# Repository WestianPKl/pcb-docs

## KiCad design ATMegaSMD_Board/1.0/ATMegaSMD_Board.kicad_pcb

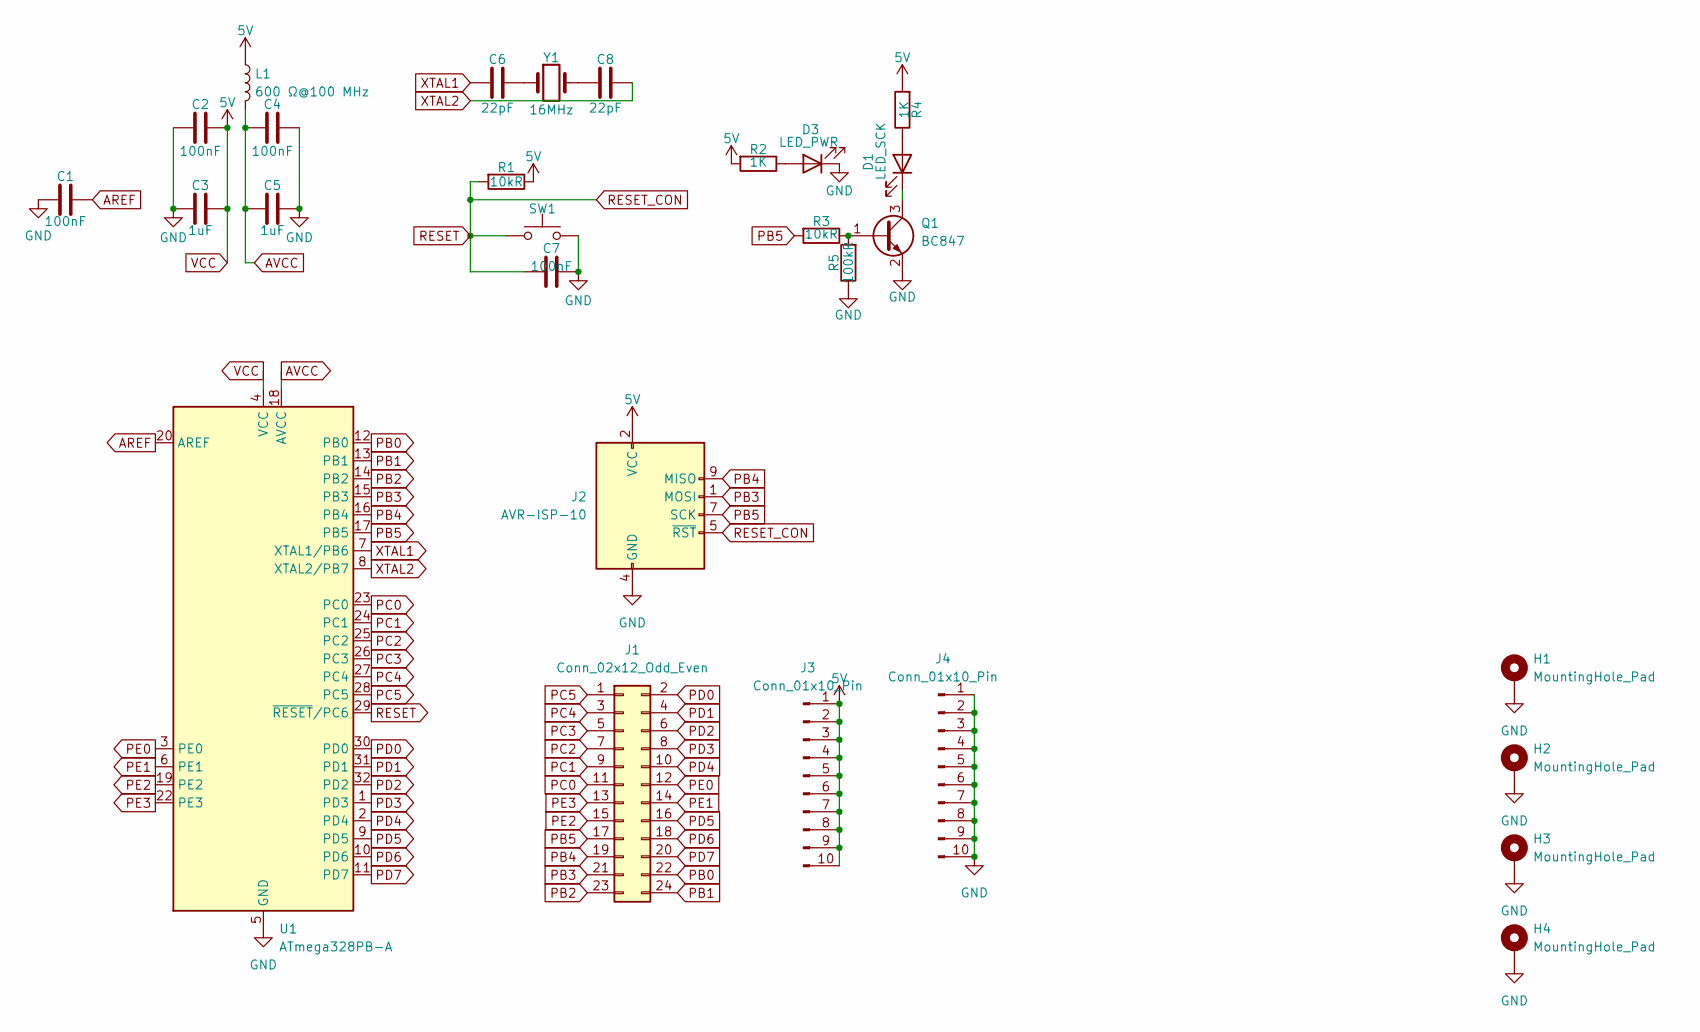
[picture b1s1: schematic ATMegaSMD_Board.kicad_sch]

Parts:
C1, C2, C4, C7: 100nF; C_0805_2012Metric_Pad1.18x1.45mm_HandSolder
C3, C5: 1uF; C_0805_2012Metric_Pad1.18x1.45mm_HandSolder
C6, C8: 22pF; C_0805_2012Metric_Pad1.18x1.45mm_HandSolder
D1: LED_SCK; LED_0805_2012Metric
D3: LED_PWR; LED_0805_2012Metric
H1, H2, H3, H4: MountingHole_Pad; MountingHole_3.2mm_M3_DIN965_Pad
J1: Conn_02x12_Odd_Even; PinHeader_2x12_P2.54mm_Vertical
J2: AVR-ISP-10; IDC-Header_2x05_P2.54mm_Vertical
J3, J4: Conn_01x10_Pin; PinHeader_1x10_P2.54mm_Vertical
L1: 600 Ω@100 MHz; L_0805_2012Metric_Pad1.05x1.20mm_HandSolder
Q1: BC847; SOT-23
R1, R3: 10kR; R_0805_2012Metric
R2, R4: 1K; R_0805_2012Metric
R5: 100kR; R_0805_2012Metric
SW1: Tact Switch 6x6mm / 13mm; SW_PUSH_6mm
U1: ATmega328PB-A; TQFP-32_7x7mm_P0.8mm
Y1: 16MHz; Crystal_HC49-4H_Vertical

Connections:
AREF: C1.2, U1.20 (AREF)
AVCC: C4.1, C5.1, L1.2, U1.18 (AVCC)
GND: C1.1, C2.1, C3.1, C4.2, C5.2, C7.2, D3.1 (K), H1.1, H2.1, H3.1, H4.1, J2.4 (GND), J2.6 (GND), J2.8 (GND), J2.10 (GND), J4.1, J4.2, J4.3, J4.4, J4.5, J4.6, J4.7, J4.8, J4.9, J4.10, Q1.2 (E), R5.1, SW1.2, U1.5 (GND), U1.21 (GND)
unnamed: C6.2, Y1.1
unnamed: C8.1, Y1.2
unnamed: D1.2 (A), R4.1
unnamed: D1.1 (K), Q1.3 (C)
unnamed: D3.2 (A), R2.1
unnamed: Q1.1 (B), R3.1, R5.2
PB0: J1.22, U1.12 (PB0)
PB1: J1.24, U1.13 (PB1)
PB2: J1.23, U1.14 (PB2)
PB3: J1.21, J2.1 (MOSI), U1.15 (PB3)
PB4: J1.19, J2.9 (MISO), U1.16 (PB4)
PB5: J1.17, J2.7 (SCK), R3.2, U1.17 (PB5)
PC0: J1.11, U1.23 (PC0)
PC1: J1.9, U1.24 (PC1)
PC2: J1.7, U1.25 (PC2)
PC3: J1.5, U1.26 (PC3)
PC4: J1.3, U1.27 (PC4)
PC5: J1.1, U1.28 (PC5)
PD0: J1.2, U1.30 (PD0)
PD1: J1.4, U1.31 (PD1)
PD2: J1.6, U1.32 (PD2)
PD3: J1.8, U1.1 (PD3)
PD4: J1.10, U1.2 (PD4)
PD5: J1.16, U1.9 (PD5)
PD6: J1.18, U1.10 (PD6)
PD7: J1.20, U1.11 (PD7)
PE0: J1.12, U1.3 (PE0)
PE1: J1.14, U1.6 (PE1)
PE2: J1.15, U1.19 (PE2)
PE3: J1.13, U1.22 (PE3)
RESET: C7.1, J2.5 (~RST), R1.2, SW1.1, U1.29 (~RESET/PC6)
VCC: C2.2, C3.2, J2.2 (VCC), J3.1, J3.2, J3.3, J3.4, J3.5, J3.6, J3.7, J3.8, J3.9, J3.10, L1.1, R1.1, R2.2, R4.2, U1.4 (VCC)
XTAL1: C6.1, U1.7 (XTAL1/PB6)
XTAL2: C8.2, U1.8 (XTAL2/PB7)

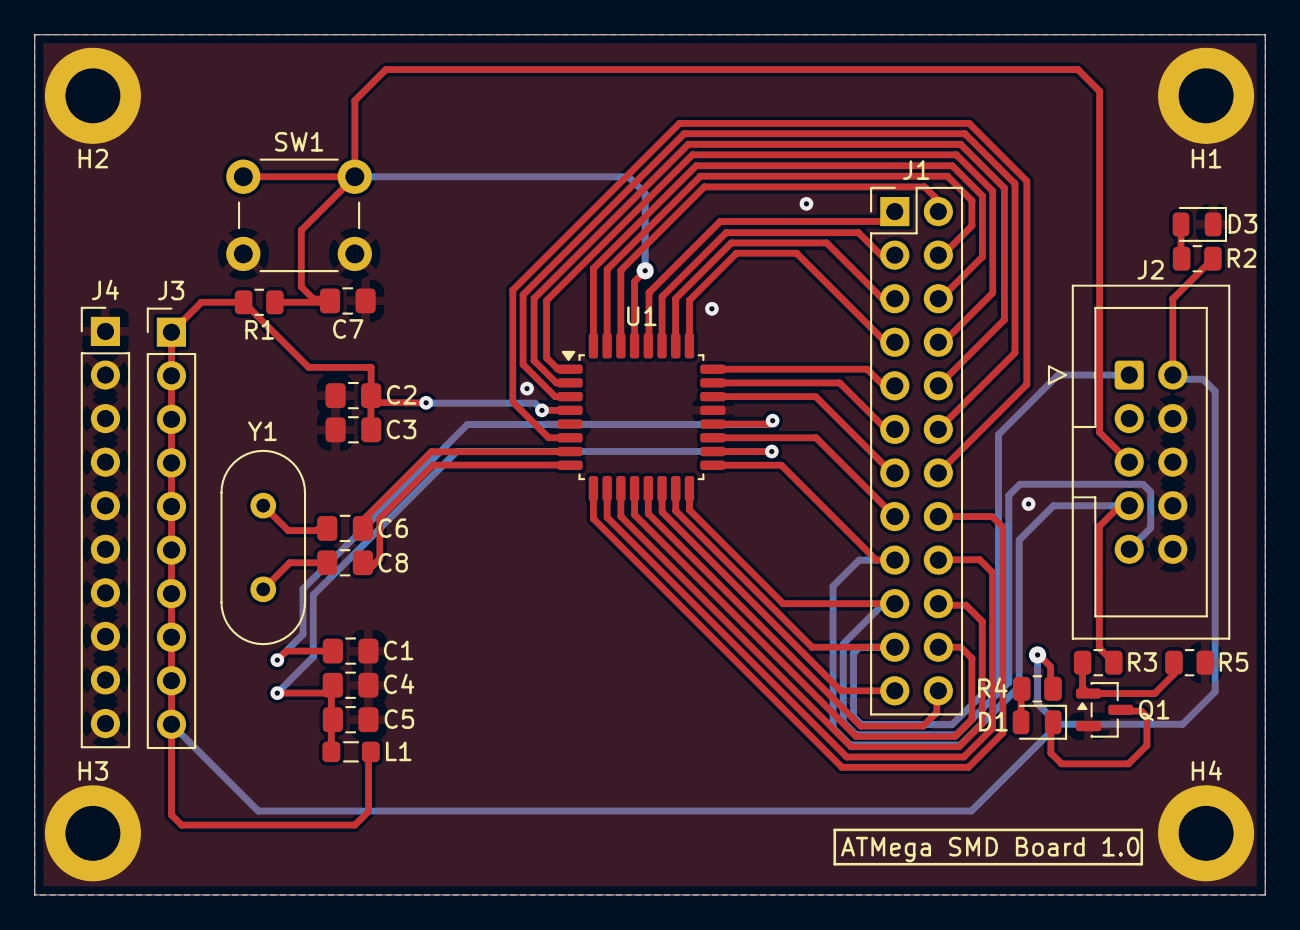
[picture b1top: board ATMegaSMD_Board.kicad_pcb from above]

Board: 2 copper layers, 71.7 x 50.2 mm, 28 parts (0 on the bottom side), 37 nets.

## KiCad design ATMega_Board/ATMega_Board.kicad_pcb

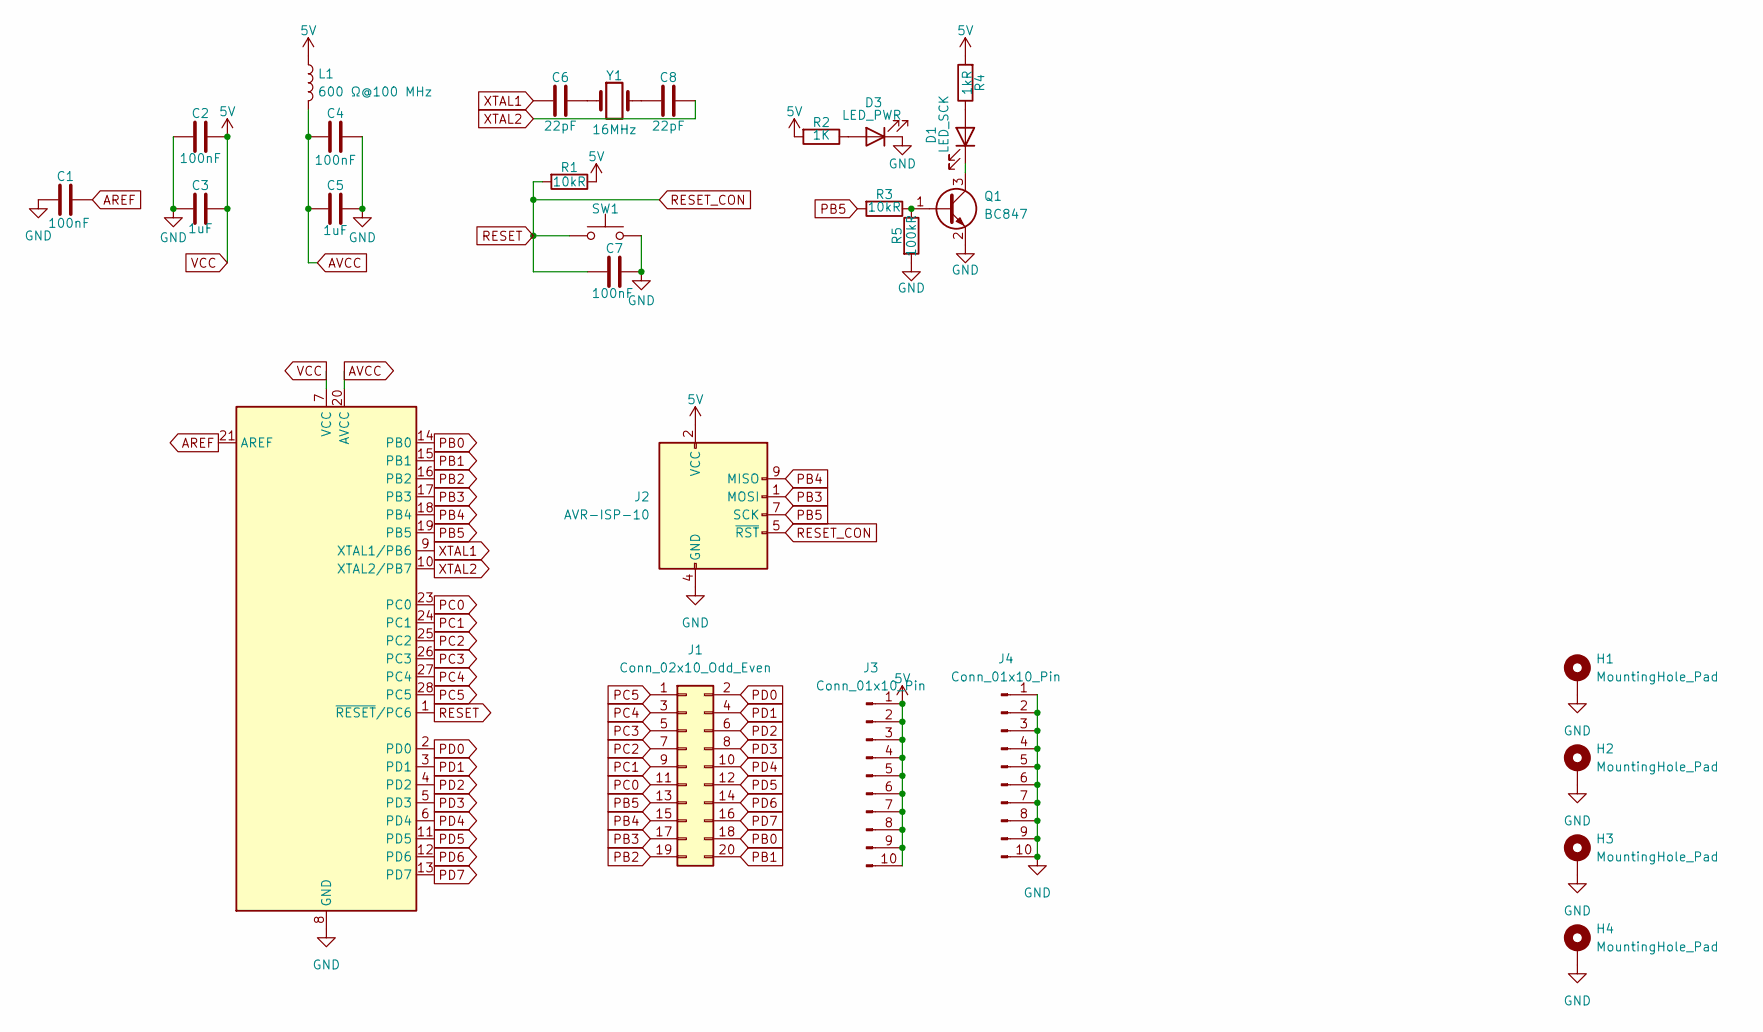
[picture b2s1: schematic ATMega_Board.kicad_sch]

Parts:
C1, C2, C4, C7: 100nF; C_0603_1608Metric
C3, C5: 1uF; C_0603_1608Metric
C6, C8: 22pF; C_0603_1608Metric
D1: LED_SCK; LED_0603_1608Metric
D3: LED_PWR; LED_0603_1608Metric
H1, H2, H3, H4: MountingHole_Pad; MountingHole_3.2mm_M3_DIN965_Pad
J1: Conn_02x10_Odd_Even; PinHeader_2x10_P2.54mm_Vertical
J2: AVR-ISP-10; IDC-Header_2x05_P2.54mm_Vertical
J3, J4: Conn_01x10_Pin; PinHeader_1x10_P2.54mm_Vertical
L1: 600 Ω@100 MHz; L_0603_1608Metric
Q1: BC847; SOT-23
R1, R3: 10kR; R_0603_1608Metric
R2: 1K; R_0603_1608Metric
R4: 1kR; R_0603_1608Metric
R5: 100kR; R_0603_1608Metric
SW1: Tact Switch 6x6mm / 13mm; SW_PUSH_6mm
U2: ATmega328P-P; DIP-28_W7.62mm
Y1: 16MHz; Crystal_HC49-4H_Vertical

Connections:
AREF: C1.2, U2.21 (AREF)
AVCC: C4.1, C5.1, L1.2, U2.20 (AVCC)
GND: C1.1, C2.1, C3.1, C4.2, C5.2, C7.2, D3.1 (K), H1.1, H2.1, H3.1, H4.1, J2.4 (GND), J2.6 (GND), J2.8 (GND), J2.10 (GND), J4.1, J4.2, J4.3, J4.4, J4.5, J4.6, J4.7, J4.8, J4.9, J4.10, Q1.2 (E), R5.2, SW1.2, U2.8 (GND), U2.22 (GND)
unnamed: C6.2, Y1.1
unnamed: C8.1, Y1.2
unnamed: D1.2 (A), R4.1
unnamed: D1.1 (K), Q1.3 (C)
unnamed: D3.2 (A), R2.1
unnamed: Q1.1 (B), R3.1, R5.1
PB0: J1.18, U2.14 (PB0)
PB1: J1.20, U2.15 (PB1)
PB2: J1.19, U2.16 (PB2)
PB3: J1.17, J2.1 (MOSI), U2.17 (PB3)
PB4: J1.15, J2.9 (MISO), U2.18 (PB4)
PB5: J1.13, J2.7 (SCK), R3.2, U2.19 (PB5)
PC0: J1.11, U2.23 (PC0)
PC1: J1.9, U2.24 (PC1)
PC2: J1.7, U2.25 (PC2)
PC3: J1.5, U2.26 (PC3)
PC4: J1.3, U2.27 (PC4)
PC5: J1.1, U2.28 (PC5)
PD0: J1.2, U2.2 (PD0)
PD1: J1.4, U2.3 (PD1)
PD2: J1.6, U2.4 (PD2)
PD3: J1.8, U2.5 (PD3)
PD4: J1.10, U2.6 (PD4)
PD5: J1.12, U2.11 (PD5)
PD6: J1.14, U2.12 (PD6)
PD7: J1.16, U2.13 (PD7)
RESET: C7.1, J2.5 (~RST), R1.2, SW1.1, U2.1 (~RESET/PC6)
VCC: C2.2, C3.2, J2.2 (VCC), J3.1, J3.2, J3.3, J3.4, J3.5, J3.6, J3.7, J3.8, J3.9, J3.10, L1.1, R1.1, R2.2, R4.2, U2.7 (VCC)
XTAL1: C6.1, U2.9 (XTAL1/PB6)
XTAL2: C8.2, U2.10 (XTAL2/PB7)

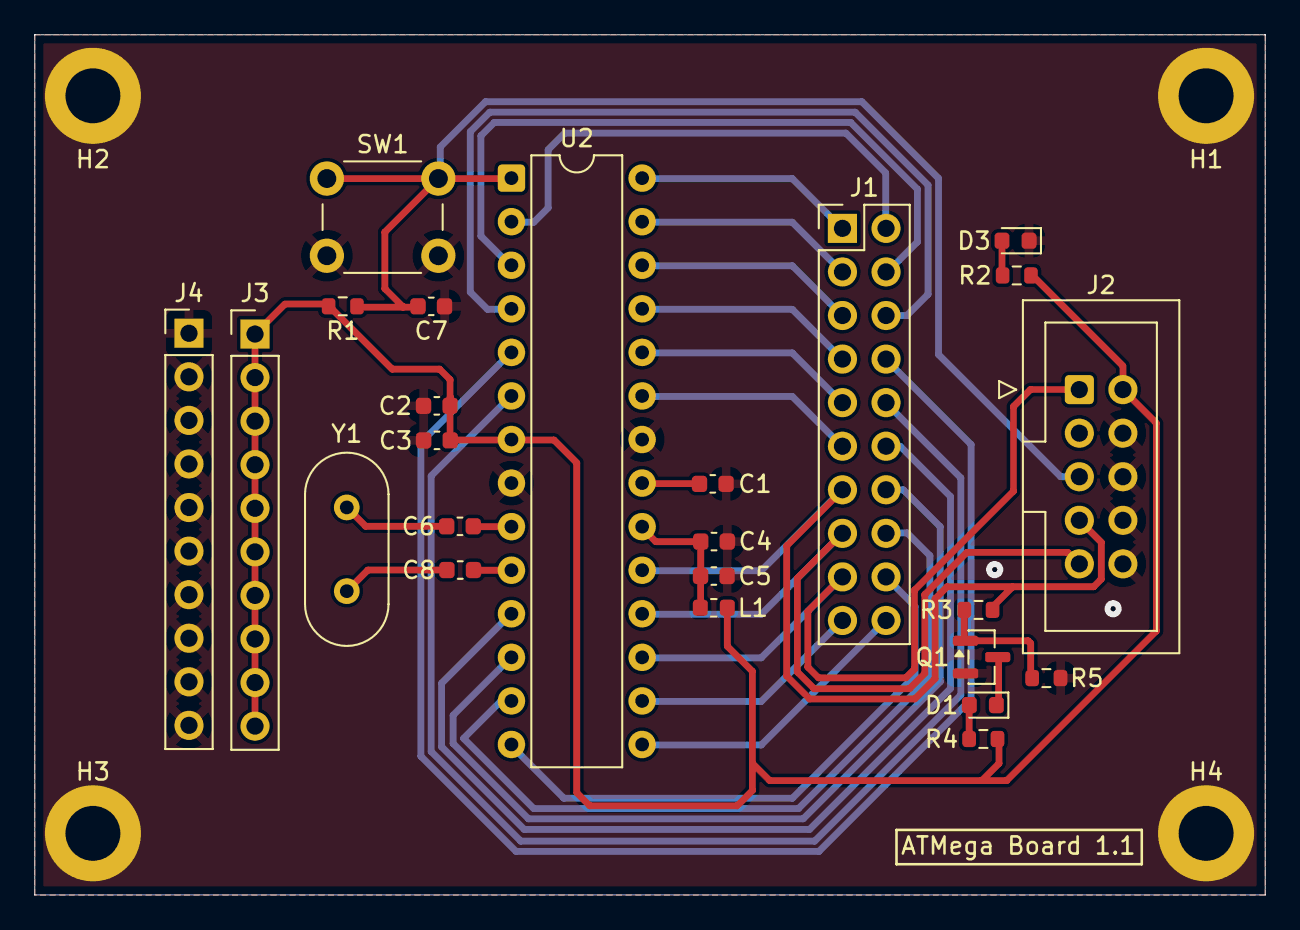
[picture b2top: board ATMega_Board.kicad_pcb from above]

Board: 2 copper layers, 71.7 x 50.2 mm, 28 parts (0 on the bottom side), 33 nets.

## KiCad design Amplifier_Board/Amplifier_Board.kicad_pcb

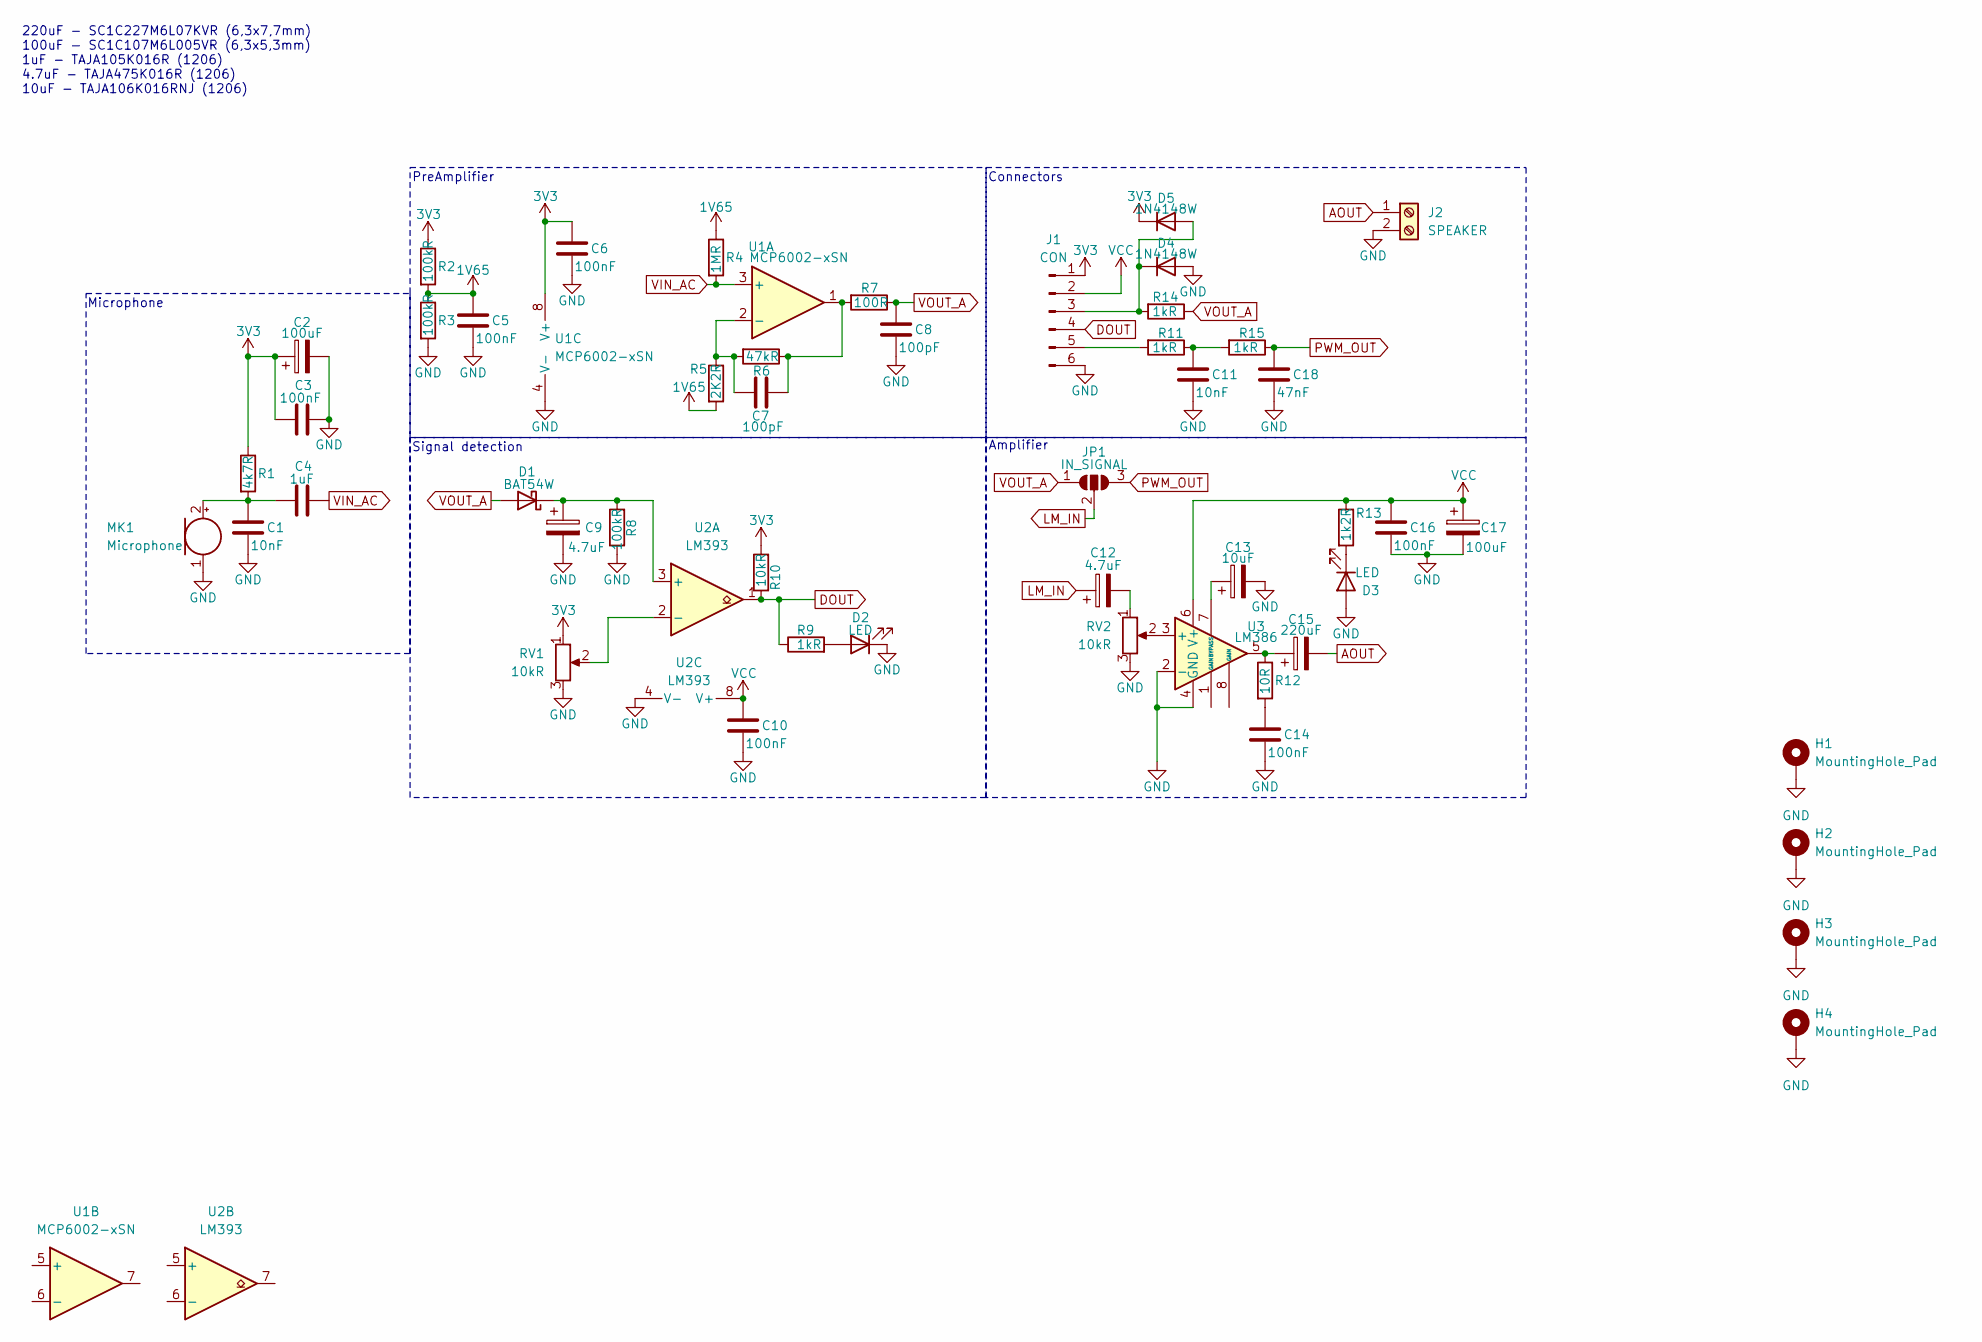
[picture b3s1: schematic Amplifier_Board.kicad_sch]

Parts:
C1, C11: 10nF; C_0805_2012Metric
C2, C17: 100uF; CP_Elec_6.3x5.3
C3, C5, C6, C10, C14, C16: 100nF; C_0805_2012Metric
C4: 1uF; C_1206_3216Metric
C7, C8: 100pF; C_0805_2012Metric
C9, C12: 4.7uF; C_1206_3216Metric
C13: 10uF; C_1206_3216Metric
C15: 220uF; CP_Elec_6.3x7.7
C18: 47nF; C_0805_2012Metric
D1: BAT54W; D_SOD-323F
D2, D3: LED; LED_0805_2012Metric
D4, D5: 1N4148W; D_SOD-123
H1, H2, H3, H4: MountingHole_Pad; MountingHole_3.2mm_M3_DIN965_Pad
J1: CON; PinHeader_1x06_P2.54mm_Vertical
J2: SPEAKER; TerminalBlock_Phoenix_MKDS-1,5-2_1x02_P5.00mm_Horizontal
JP1: IN_SIGNAL; PinHeader_1x03_P2.54mm_Vertical
MK1: Microphone; POM-2244P-C3310-2-R
R1: 4k7R; R_0805_2012Metric
R2, R3, R8: 100kR; R_0805_2012Metric
R4: 1MR; R_0805_2012Metric
R5: 2K2R; R_0805_2012Metric
R6: 47kR; R_0805_2012Metric
R7: 100R; R_0805_2012Metric
R9, R11, R14, R15: 1kR; R_0805_2012Metric
R10: 10kR; R_0805_2012Metric
R12: 10R; R_0805_2012Metric
R13: 1k2R; R_0805_2012Metric
RV1, RV2: 10kR; Potentiometer_Runtron_RM-065_Vertical
U1: MCP6002-xSN; SOIC-8_3.9x4.9mm_P1.27mm
U2: LM393; SOIC-8_3.9x4.9mm_P1.27mm
U3: LM386; SOIC-8_3.9x4.9mm_P1.27mm

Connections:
1V65: C5.1, R2.2, R3.1, R4.1, R5.2
3V3: C2.1, C3.2, C6.1, D5.1 (K), J1.1, R1.1, R2.1, R10.2, RV1.1, U1.8 (V+)
AOUT: C15.2, J2.1
DOUT: J1.4, R9.1, R10.1, U2.1
GND: C1.2, C2.2, C3.1, C5.2, C6.2, C8.2, C9.2, C10.2, C11.2, C13.2, C14.2, C16.2, C17.2, C18.2, D2.1 (K), D3.2 (A), D4.2 (A), H1.1, H2.1, H3.1, H4.1, J1.6, J2.2, MK1.1 (-), R3.2, R8.1, RV1.3, RV2.3, U1.4 (V-), U2.4 (V-), U3.2 (-), U3.4 (GND)
LM_IN: C12.1, JP1.2 (C)
unnamed: C7.2, R6.1, R7.2, U1.1
unnamed: C11.1, R11.1, R15.2
unnamed: C12.2, RV2.1
unnamed: C14.1, R12.2
unnamed: C15.1, R12.1, U3.5
unnamed: C9.1, D1.1 (K), R8.2, U2.3 (+)
unnamed: D2.2 (A), R9.2
unnamed: D3.1 (K), R13.2
unnamed: D4.1 (K), D5.2 (A), J1.3, R14.2
unnamed: J1.5, R11.2
unnamed: C1.1, C4.2, MK1.2 (+), R1.2
unnamed: C7.1, R5.1, R6.2, U1.2 (-)
unnamed: RV1.2, U2.2 (-)
unnamed: RV2.2, U3.3 (+)
unnamed: C13.1, U3.7 (BYPASS)
PWM_OUT: C18.1, JP1.3 (B), R15.1
VCC: C10.1, C16.1, C17.1, J1.2, R13.1, U2.8 (V+), U3.6 (V+)
VIN_AC: C4.1, R4.2, U1.3 (+)
VOUT_A: C8.1, D1.2 (A), JP1.1 (A), R7.1, R14.1

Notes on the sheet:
220uF - SC1C227M6L07KVR (6,3x7,7mm) 100uF - SC1C107M6L005VR (6,3x5,3mm) 1uF - TAJA105K016R (1206) 4.7uF - TAJA475K016R (1206) 10uF - TAJA106K016RNJ (1206)
Signal detection
PreAmplifier
Amplifier
Microphone
Connectors

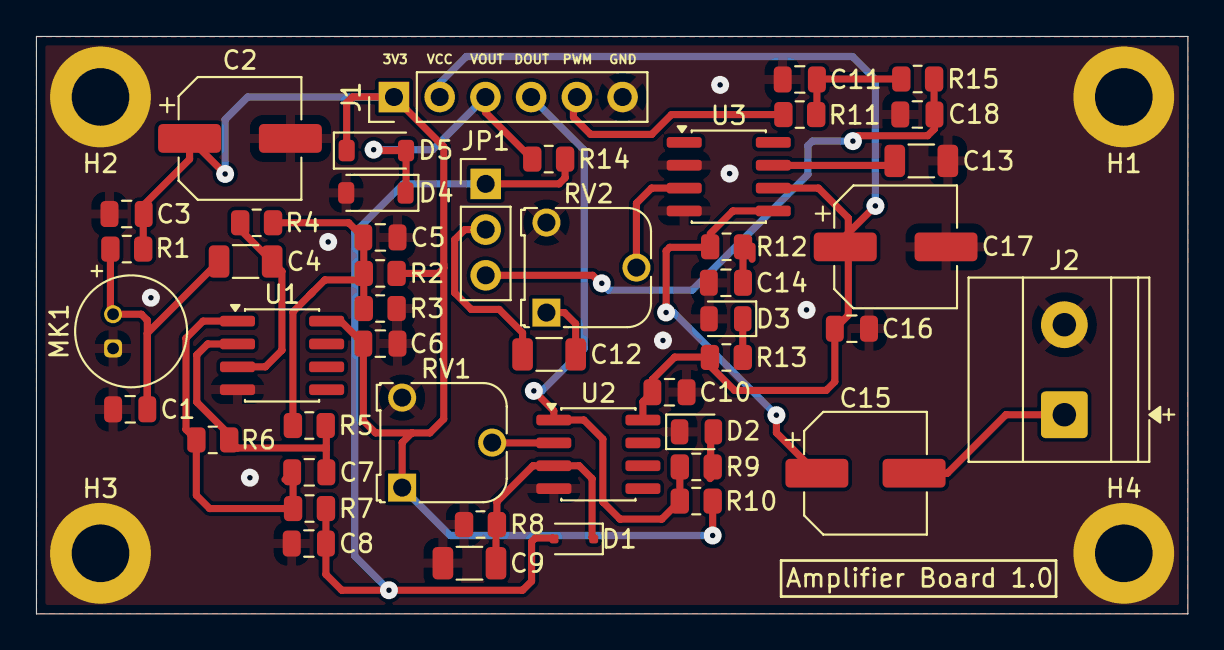
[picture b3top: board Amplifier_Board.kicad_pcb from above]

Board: 2 copper layers, 64.0 x 32.1 mm, 51 parts (0 on the bottom side), 25 nets.

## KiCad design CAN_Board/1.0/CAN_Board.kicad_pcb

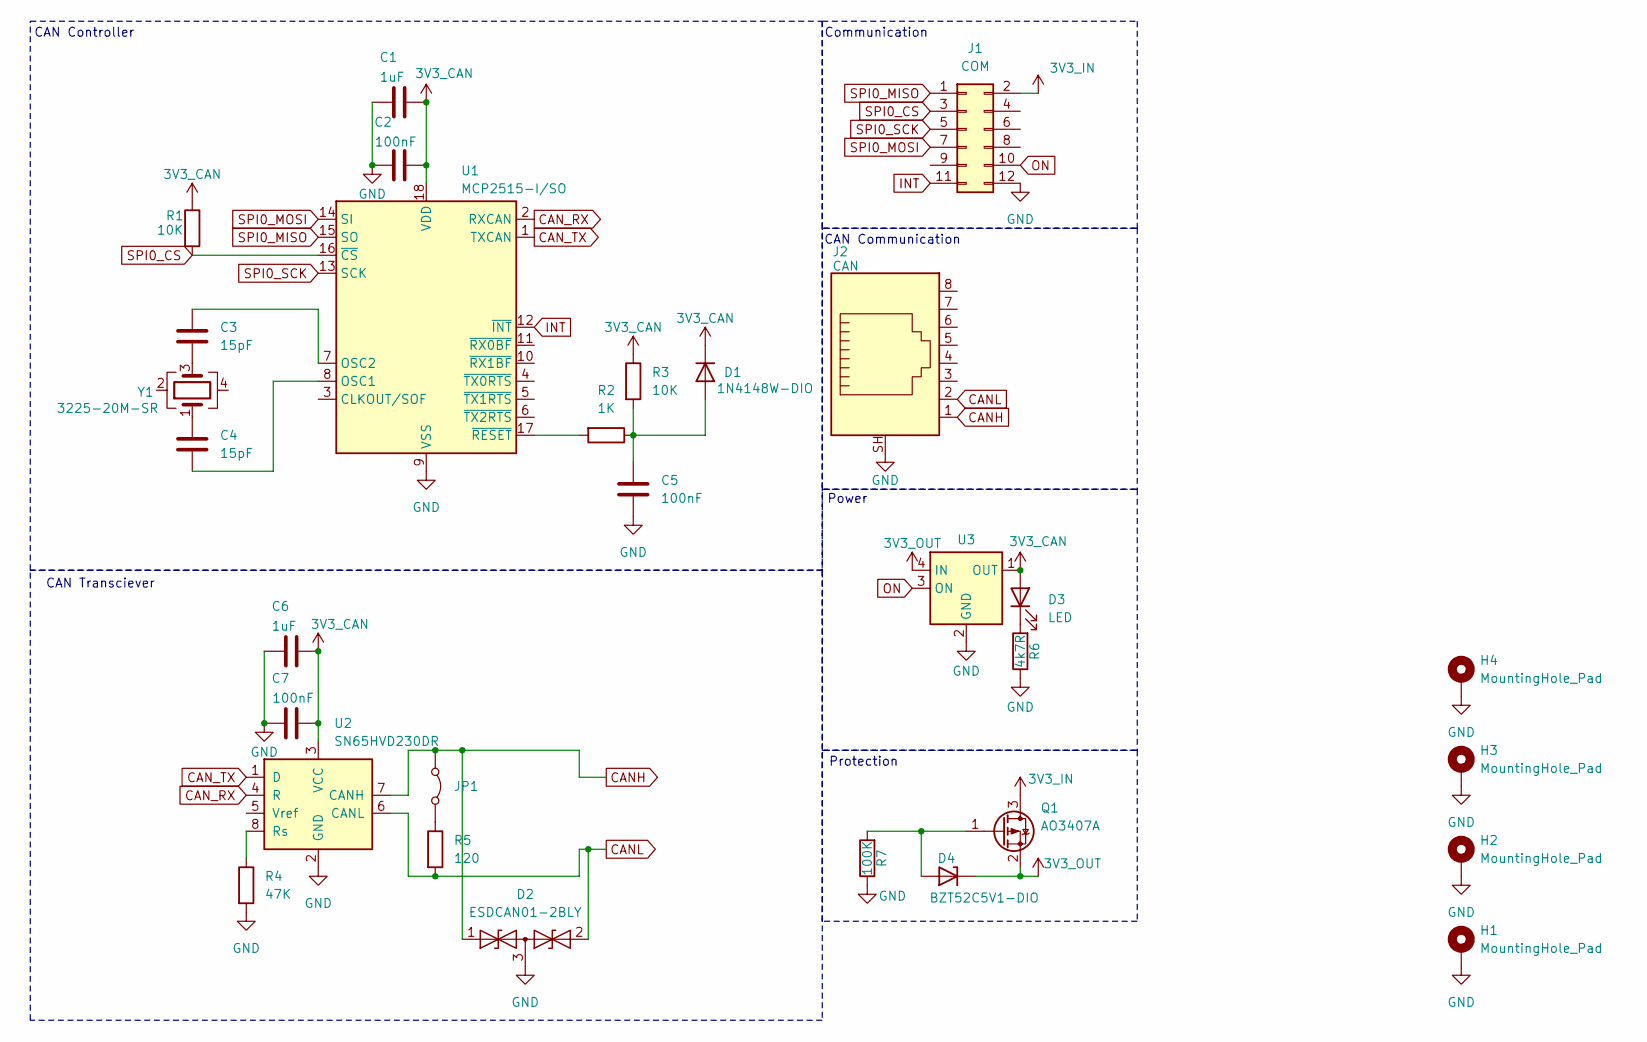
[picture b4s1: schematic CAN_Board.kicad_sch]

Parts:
C1, C6: 1uF; C_0603_1608Metric
C2, C5, C7: 100nF; C_0805_2012Metric
C3, C4: 15pF; C_0805_2012Metric
D1: 1N4148W-DIO; D_SOD-123F
D2: ESDCAN01-2BLY; SOT-23
D3: LED; LED_0805_2012Metric
D4: BZT52C5V1-DIO; D_SOD-123F
H1, H2, H3, H4: MountingHole_Pad; MountingHole_3.2mm_M3_DIN965_Pad
J1: COM; PinHeader_2x06_P2.54mm_Vertical
J2: CAN; RJ45_Amphenol_RJHSE5380
JP1: Jumper_2_Bridged; PinHeader_1x02_P2.54mm_Vertical
Q1: AO3407A; SOT-23
R1, R3: 10K; R_0805_2012Metric
R2: 1K; R_0805_2012Metric
R4: 47K; R_0805_2012Metric
R5: 120; R_0805_2012Metric
R6: 4k7R; R_0805_2012Metric
R7: 100K; R_0805_2012Metric
U1: MCP2515-I/SO; SOIC-18W_7.5x11.6mm_P1.27mm
U2: SN65HVD230DR; SOIC-8_3.9x4.9mm_P1.27mm
U3: SIP32431DR3-T1GE3; SOT-363_SC-70-6
Y1: 3225-20M-SR; Crystal_SMD_3225-4Pin_3.2x2.5mm

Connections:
3V3_CAN: C1.1, C2.1, C6.1, C7.1, D1.1 (K), D3.2 (A), R1.1, R3.1, U1.18 (VDD), U2.3 (VCC), U3.1 (OUT)
3V3_IN: J1.2, Q1.3 (D)
3V3_OUT: D4.1 (K), Q1.2 (S), U3.4 (IN)
CANH: D2.1 (A1), J2.1, JP1.1 (A), U2.7 (CANH)
CANL: D2.2 (A2), J2.2, R5.2, U2.6 (CANL)
CAN_RX: U1.2 (RXCAN), U2.4 (R)
CAN_TX: U1.1 (TXCAN), U2.1 (D)
GND: C1.2, C2.2, C5.2, C6.2, C7.2, D2.3 (common), H1.1, H2.1, H3.1, H4.1, J1.12, J2.SH, R4.2, R6.1, R7.1, U1.9 (VSS), U2.2 (GND), U3.2 (GND), U3.5 (GND)
INT: J1.11, U1.12 (~INT)
unnamed: C3.2, Y1.3
unnamed: C4.1, Y1.1
unnamed: C5.1, D1.2 (A), R2.1, R3.2
unnamed: D3.1 (K), R6.2
unnamed: D4.2 (A), Q1.1 (G), R7.2
unnamed: JP1.2 (B), R5.1
unnamed: C4.2, U1.8 (OSC1)
unnamed: C3.1, U1.7 (OSC2)
unnamed: R2.2, U1.17 (~RESET)
unnamed: R4.1, U2.8 (Rs)
ON: J1.10, U3.3 (ON)
SPI0_CS: J1.3, R1.2, U1.16 (~CS)
SPI0_MISO: J1.1, U1.15 (SO)
SPI0_MOSI: J1.7, U1.14 (SI)
SPI0_SCK: J1.5, U1.13 (SCK)

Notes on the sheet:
CAN Controller
Communication
CAN Communication
CAN Transciever
Protection
Power

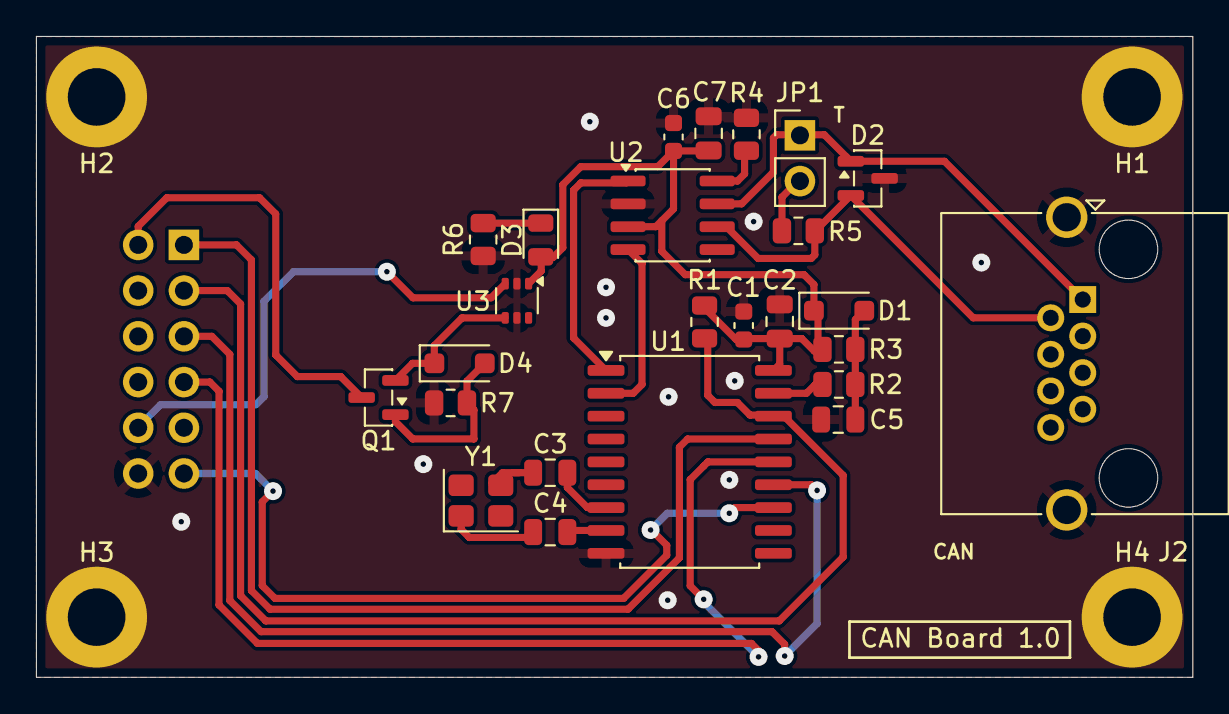
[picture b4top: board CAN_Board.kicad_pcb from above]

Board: 2 copper layers, 64.2 x 35.6 mm, 30 parts (1 on the bottom side), 24 nets.

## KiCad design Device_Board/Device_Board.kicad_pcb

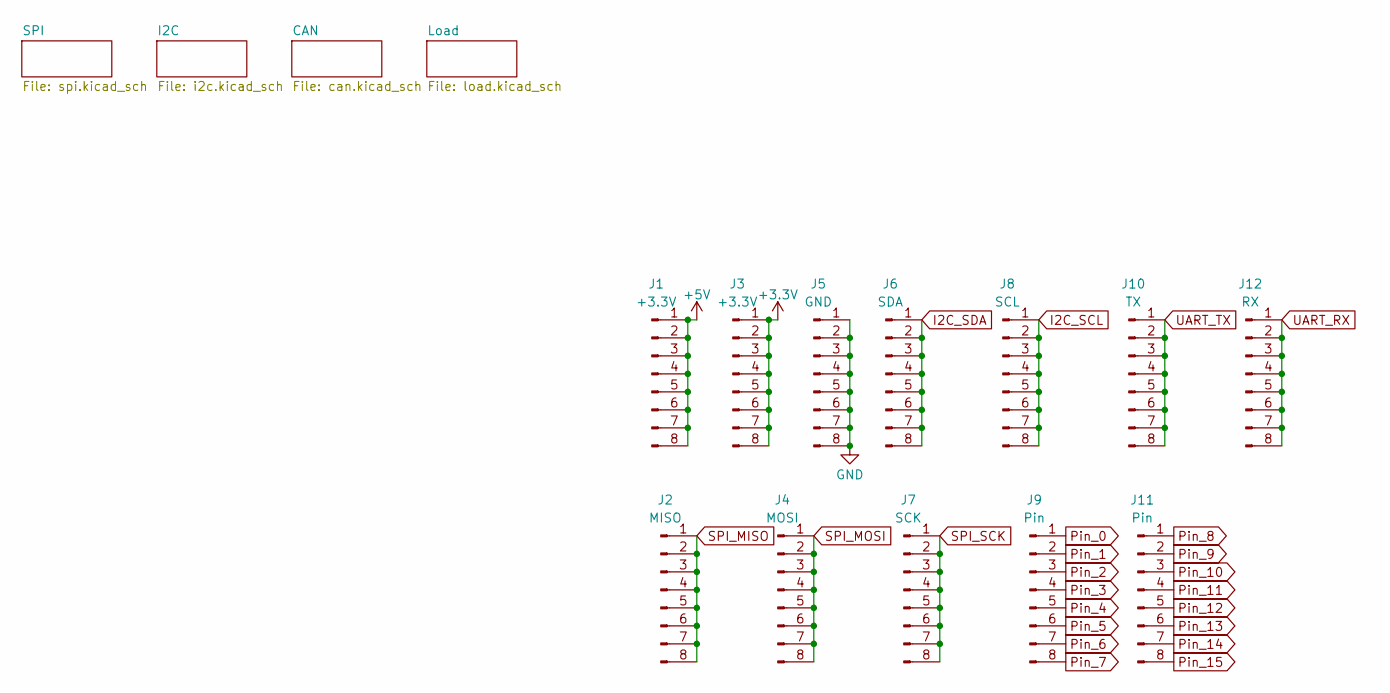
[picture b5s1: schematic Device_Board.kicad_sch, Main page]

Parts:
J1, J3: +3.3V; PinHeader_1x08_P2.54mm_Vertical
J2: MISO; PinHeader_1x08_P2.54mm_Vertical
J4: MOSI; PinHeader_1x08_P2.54mm_Vertical
J5: GND; PinHeader_1x08_P2.54mm_Vertical
J6: SDA; PinHeader_1x08_P2.54mm_Vertical
J7: SCK; PinHeader_1x08_P2.54mm_Vertical
J8: SCL; PinHeader_1x08_P2.54mm_Vertical
J9, J11: Pin; PinHeader_1x08_P2.54mm_Vertical
J10: TX; PinHeader_1x08_P2.54mm_Vertical
J12: RX; PinHeader_1x08_P2.54mm_Vertical

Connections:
+3.3V: J3.1, J3.2, J3.3, J3.4, J3.5, J3.6, J3.7, J3.8; also elsewhere on the board
+5V: J1.1, J1.2, J1.3, J1.4, J1.5, J1.6, J1.7, J1.8; also elsewhere on the board
GND: J5.1, J5.2, J5.3, J5.4, J5.5, J5.6, J5.7, J5.8; also elsewhere on the board
I2C_SCL: J8.1, J8.2, J8.3, J8.4, J8.5, J8.6, J8.7, J8.8; also elsewhere on the board
I2C_SDA: J6.1, J6.2, J6.3, J6.4, J6.5, J6.6, J6.7, J6.8; also elsewhere on the board
Pin_0: J9.1; also elsewhere on the board
Pin_1: J9.2; also elsewhere on the board
Pin_2: J9.3; also elsewhere on the board
Pin_3: J9.4; also elsewhere on the board
Pin_4: J9.5; also elsewhere on the board
Pin_5: J9.6; also elsewhere on the board
Pin_6: J9.7; also elsewhere on the board
Pin_7: J9.8; also elsewhere on the board
Pin_8: J11.1; also elsewhere on the board
Pin_9: J11.2; also elsewhere on the board
Pin_10: J11.3; also elsewhere on the board
Pin_11: J11.4; also elsewhere on the board
Pin_12: J11.5; also elsewhere on the board
Pin_13: J11.6; also elsewhere on the board
Pin_14: J11.7; also elsewhere on the board
Pin_15: J11.8; also elsewhere on the board
SPI_MISO: J2.1, J2.2, J2.3, J2.4, J2.5, J2.6, J2.7, J2.8; also elsewhere on the board
SPI_MOSI: J4.1, J4.2, J4.3, J4.4, J4.5, J4.6, J4.7, J4.8; also elsewhere on the board
SPI_SCK: J7.1, J7.2, J7.3, J7.4, J7.5, J7.6, J7.7, J7.8; also elsewhere on the board
UART_RX: J12.1, J12.2, J12.3, J12.4, J12.5, J12.6, J12.7, J12.8
UART_TX: J10.1, J10.2, J10.3, J10.4, J10.5, J10.6, J10.7, J10.8

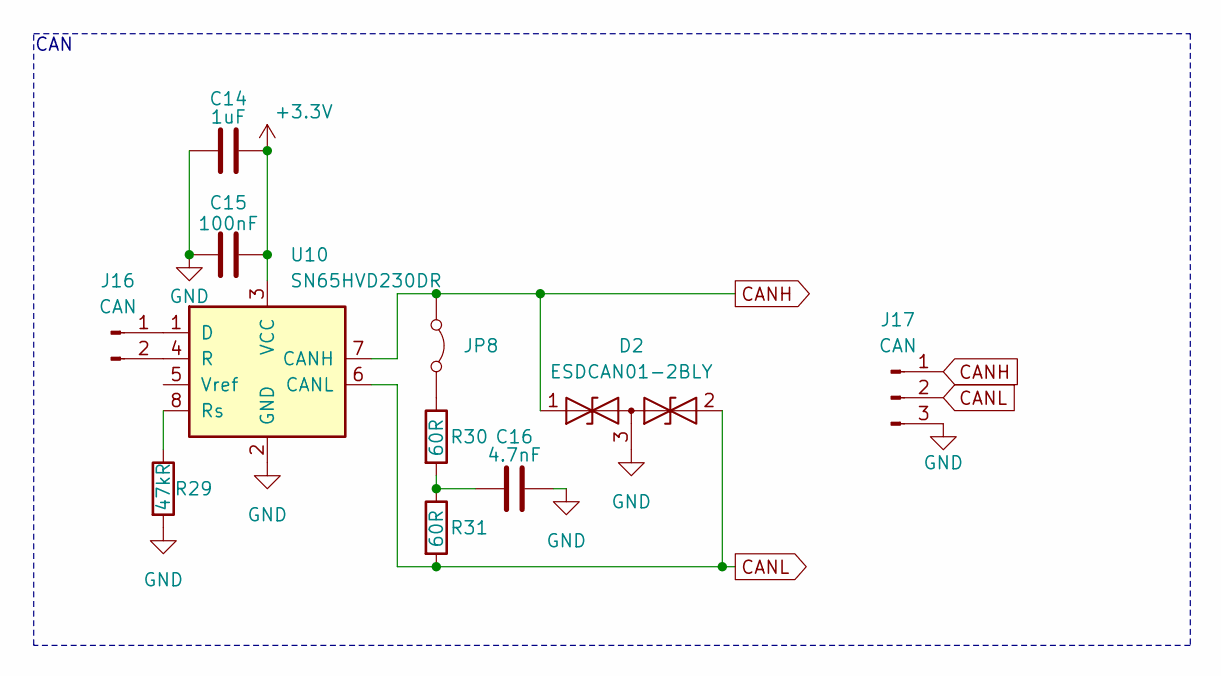
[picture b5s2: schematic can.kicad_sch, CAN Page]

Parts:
C14: 1uF; C_0603_1608Metric
C15: 100nF; C_0603_1608Metric
C16: 4.7nF; C_0603_1608Metric
D2: ESDCAN01-2BLY; SOT-23
J16: CAN; PinHeader_1x02_P2.54mm_Vertical
J17: CAN; PinHeader_1x03_P2.54mm_Vertical
JP8: Jumper_2_Bridged; PinHeader_1x02_P2.54mm_Vertical
R29: 47kR; R_0603_1608Metric
R30, R31: 60R; R_0603_1608Metric
U10: SN65HVD230DR; SOIC-8_3.9x4.9mm_P1.27mm

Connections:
+3.3V: C14.1, C15.1, U10.3 (VCC); also elsewhere on the board
CANH: D2.1 (A1), J17.1, JP8.1 (A), U10.7 (CANH)
CANL: D2.2 (A2), J17.2, R31.2, U10.6 (CANL)
GND: C14.2, C15.2, C16.1, D2.3 (common), J17.3, R29.2, U10.2 (GND); also elsewhere on the board
unnamed: C16.2, R30.2, R31.1
unnamed: J16.1, U10.1 (D)
unnamed: J16.2, U10.4 (R)
unnamed: JP8.2 (B), R30.1
unnamed: R29.1, U10.8 (Rs)

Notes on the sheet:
CAN
